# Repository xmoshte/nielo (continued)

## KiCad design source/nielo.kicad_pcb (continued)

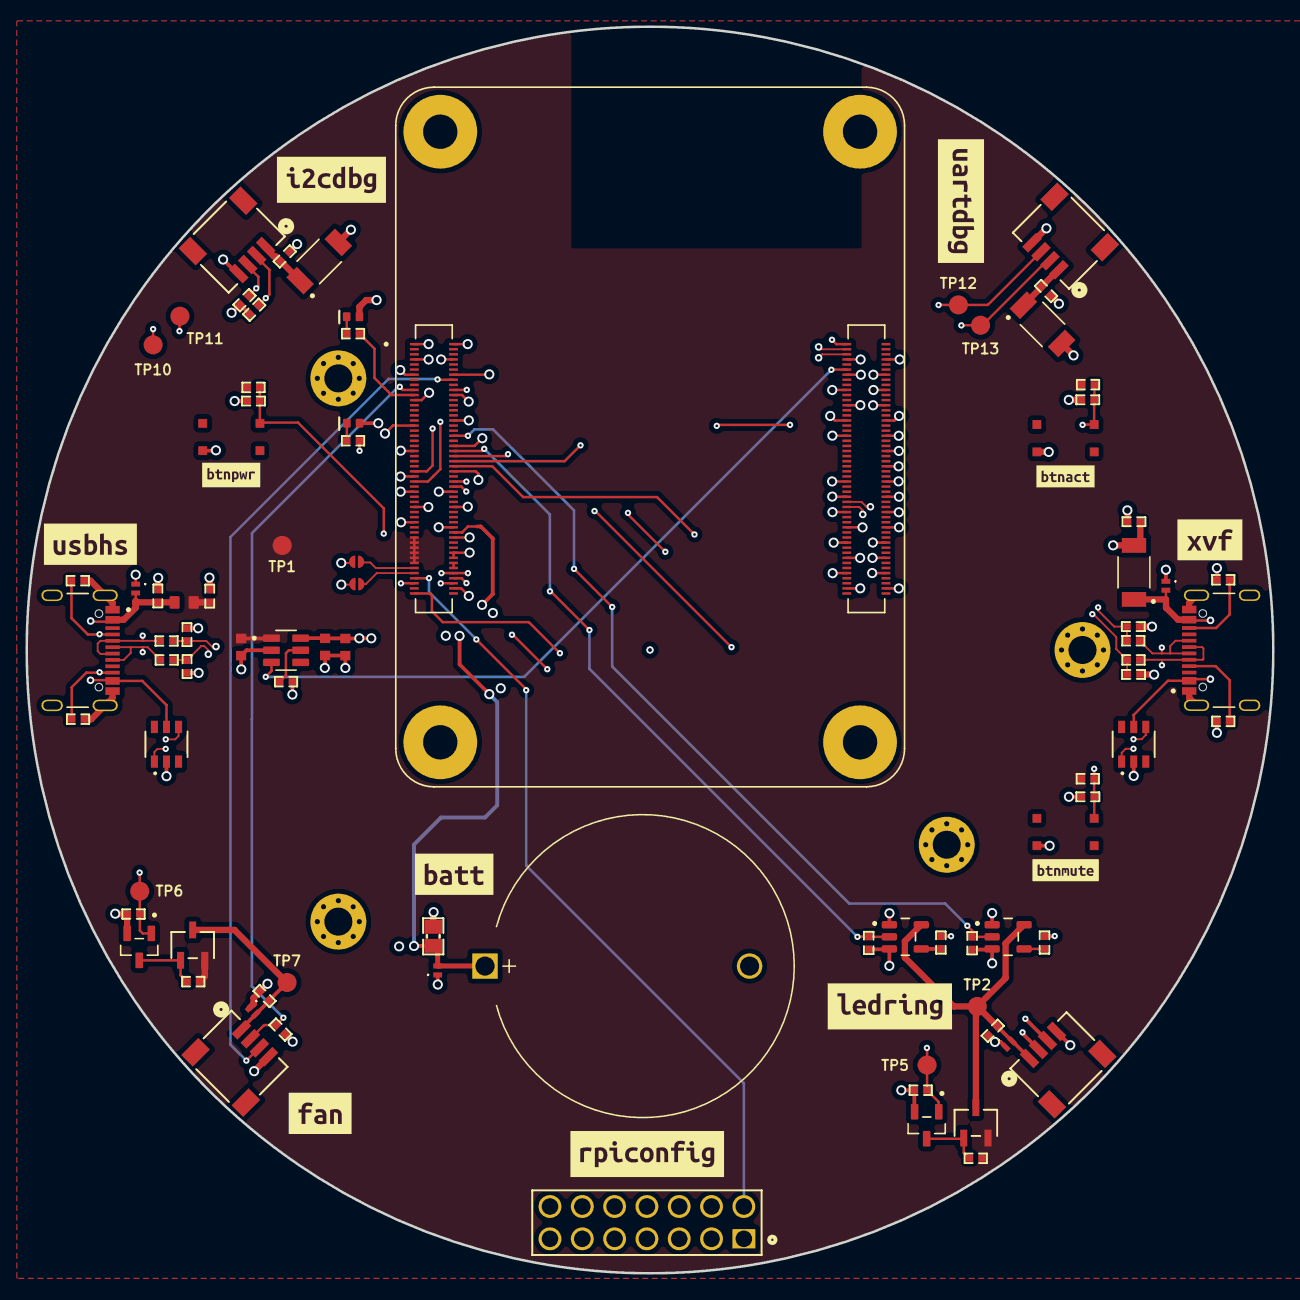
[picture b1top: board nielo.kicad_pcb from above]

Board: 6 copper layers, 98.0 x 98.0 mm, 101 parts (1 on the bottom side), 54 nets.

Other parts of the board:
kibuzzard-6AB7D9C9: G***; kibuzzard-6AB7D9C9
kibuzzard-6AB23A8A: G***; kibuzzard-6AB23A8A
kibuzzard-6AB23B9E: G***; kibuzzard-6AB23B9E
kibuzzard-6AB23B67: G***; kibuzzard-6AB23B67
kibuzzard-6AB23B87: G***; kibuzzard-6AB23B87
kibuzzard-6AB23BC6: G***; kibuzzard-6AB23BC6
kibuzzard-6AB23BDC: G***; kibuzzard-6AB23BDC
kibuzzard-6AB23C12: G***; kibuzzard-6AB23C12
kibuzzard-6AB23C23: G***; kibuzzard-6AB23C23
kibuzzard-6AB23C57: G***; kibuzzard-6AB23C57
kibuzzard-6AB24C6E: G***; kibuzzard-6AB24C6E

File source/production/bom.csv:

"Reference","Qty","Value","Description","MPN","Mouser No","DigiKey No","LCSC No"
"C18","1","10u 50V","10u 25V Capacitor Ceramic 0805","KGM21FS61E106KU","581-KGM21FS61E106KU ","478-KGM21FS61E106KUTR-ND",""
"HS1","1","SC1752","Heat Sink Raspberry Pi 5 Aluminum Top Mount","SC1752","358-SC1752","2648-SC1752-ND",""
"U2","1","SC1556","Single Board Computer 2.4GHz 4 Core 2GB/0GB RAM ARM® Cortex®-A76","SC1556","358-SC1556","2648-SC1556-ND",""
"U6,U7","2","SN74AHCT1G125DBVR","Single 4.5-V to 5.5-V buffer with TTL-compatible CMOS inputs and 3-state outputs","SN74AHCT1G125DBVR","595-SNAHCT1G125DBVR","296-4708-2-ND","C7484"
"Q1,Q4","2","AO3401A","-4.0A Id, -30V Vds, P-Channel MOSFET, SOT-23","AO3401A","","785-1001-2-ND","C15127"
"FB1","1","BLM18AG601SN1D","Ferrite Beads 600 OHM 25% Alternate Sizing Guide Below","BLM18AG601SN1D","81-BLM11A601S","490-1014-2-ND","C19330"
"D4","1","16-213/GHC-YR1S1/3T","LED EMERALD GREEN WATER CLEAR 0402 SMD","16-213/GHC-YR1S1/3T","638-16213GHCYR1S13T","1080-16-213/GHC-YR1S1/3TTR-ND","C74338"
"J5,J6,J7,J8","4","SM04B-SRSS-TB","CONN HEADER SMD R/A 4POS 1mm","SM04B-SRSS-TB","306-SM04BSRSSTBLFSN","455-SM04B-SRSS-TBTR-ND","C160404"
"J1,J2","2","TYPE-C-31-M-12","USB Type C Connector Horizontal SMT","TYPE-C-31-M-12","","","C165948"
"R11,R12,R15,R16,R17,R18","6","100k","100k Resistor Ceramic 0402","CR0402-JW-104GLF","652-CR0402JW-104GLF","CR0402-JW-104GLFTR-ND","C203104"
"J3","1","PZ254V-12-14P","CONN HEADER 14POS 2.54mm DUAL ROW TH","PZ254V-12-14P","","","C492424"
"Q2,Q3","2","2N7002","Mosfet Array 2 N-Channel (Dual) 60V 300mA 500mW Surface Mount PG-SOT363-6","2N7002","512-2N7002","2N7002NCT-ND","C916396"
"R20,R21","2","4k7","4.7k Resistor Ceramic 0402","RCA04024K70FKED","594-RCA04024K70FKED","541-RCA04024K70FKEDSRTR-ND","C1858949"
"R6,R19,R22,R23","4","10k","10k Resistor Ceramic 0402","MCS0402MD1002BE500","594-MCS0402MD1002BE5","749-MCS0402MD1002BE500TR-ND","C2073498"
"R5","1","15k 1%","15k 1% Resistor Ceramic 0402","MCS04020C1502FE500","594-MCS04020C1502FE5","749-MCS04020C1502FE500TR-ND","C2074222"
"R13,R14","2","33R","33R Resistor Ceramic 0402","MCS0402MC3309FE000"," 594-MCS0402MC3309FE0","749-MCS0402MC3309FE000TR-ND","C2074234"
"R3,R4,R7,R8","4","22R","22R Resistor Ceramic 0402","CR0402-JW-220GLF","652-CR0402-JW-220GLF","CR0402-JW-220GLFTR-ND","C2076445"
"R9,R10","2","1k","1k Resistor Ceramic 0402","CRCW04021K65FKEE","71-CRCW04021K65FKEE","","C2076615"
"R24,R25","2","12k","12k Resistor Ceramic 0402","CR0402-FX-1202GLF","652-CR0402FX-1202GLF","CR0402-FX-1202GLFTR-ND","C2085429"
"R1,R2","2","5k1","5.1k Resistor Ceramic 0402","TNPW04025K10BEED","71-TNPW04025K10BEED","541-3156-2-ND","C2088796"
"U5","1","AP22653W6-7","USB Power Switch Single 5.5V 0.125A to 2.665A 6-Pin SOT-26 T/R","AP22653W6-7","621-AP22653W6-7","31-AP22653W6-7TR-ND","C2158037"
"C1,C2,C5,C8,C12,C13,C14,C15,C16,C17","10","100n 50V","100n 50V Capacitor Ceramic 0402","04025C104JAT2A","581-04025C104JAT2A","478-KGM05CR71H104JHTR-ND","C2169023"
"C11","1","100n 50V","100n 50V Capacitor Ceramic 0603","CML0603X7R104KT50V","708-CML0603X7R104K50","738-CML0603X7R104KT50VTR-ND","C2594245"
"SW1,SW2,SW3","3","Tactile Switch","Tactile Switches Tact Switch, 12 VDC, 50 mA, 4.2x3.2, 2.5mm H, 180gf, J leadspp SPST","PTS815SJM250SMTRLFS","611-PTS815SJM250SMTR","CKN12215-2-ND","C2689510"
"U1,U3","2","USBLC6-2SC6Y","Automotive very low capacitance ESD protection","USBLC6-2SC6Y","511-USBLC6-2SC6Y","497-11882-2-ND","C2969755"
"BT1","1","BS-07-A1BJ001","Single cell battery holder","BS-07-A1BJ001","","","C2979167"
"J4,J9","2","10164227-1001A1RLF","BergStak 0.40mm, 100 position, Receptacle, 1.5mm stack height","10164227-1001A1RLF","649-01642271001A1RLF","609-10164227-1001A1RLFTR-ND","C6782225"
"C9,C10","2","10u 25V","10u 25V Capacitor Ceramic 0603","CC0603KRX5R8BB106","603-CC0603KRX5R8BB10","13-CC0603KRX5R8BB106TR-ND","C7500379"
"B1,B2,B3,B4,B5","5","PESD5V5C1BLYL","Extremely low clamping bidirectional ESD protection diode@en-us","PESD5V5C1BLYL","771-PESD5V5C1BLYL","1727-PESD5V5C1BLYLTR-ND","C18212174"
"D2,D5,D6","3","SS54FSH","5A, 40V, Schottky Rectifier","SS54FSH","821-SS54FSH","1801-SS54FSHTR-ND","C19855357"
"D3","1","YLED0402R","LED 0402 RED SMD","YLED0402R","","","C21260817"
